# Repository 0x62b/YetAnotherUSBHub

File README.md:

# YetAnotherUSBHub
A 4-port low cost USB 2.0 hub with upstream USB-C and downstream USB-A x2, USB-C, and microSD.
wip onshape: https://cad.onshape.com/documents/d3076bcf5bdf960a68612e95/w/1076ab7133259d721c6eb065/e/0b541aa8461793eb55190b47?renderMode=0&uiState=6a0653a430b61269bd2de70a

## Repo Structure
`cad`: CAD files\
`pcb`: The KiCad PCB design files, and gerbers in `pcb/production`\
`bom.csv`: The BOM needed to assemble the PCB\

## BOM
|Item                               |Unit Price (AUD)|Quantity|Extended Price (AUD)|Extended Price (USD)       |Notes      |Link                                                 |
|-----------------------------------|----------------|--------|--------------------|---------------------------|-----------|-----------------------------------------------------|
|100nF 0402 capacitor               |0               |2       |0                   |0                          |Owned      |https://www.lcsc.com/product-detail/C60474.html      |
|10uF 0402 capacitor                |0               |7       |0                   |0                          |Owned      |https://www.lcsc.com/product-detail/C315248.html     |
|onsemi NSR0320MW2T1G               |0.16            |10      |1.6                 |1.18                       |MOQ 10     |https://www.lcsc.com/product-detail/C48192.html      |
|Green 0402 LED                     |0               |1       |0                   |0                          |Owned      |https://www.lcsc.com/product-detail/C598352.html     |
|Molex 67643-2911                   |1.34            |2       |2.68                |1.92                       |N/A        |https://www.lcsc.com/product-detail/C293351.html     |
|Molex 104031-0811                  |1.05            |1       |1.05                |0.75                       |N/A        |https://www.lcsc.com/product-detail/C585350.html     |
|Korean Hroparts Elec TYPE-C-31-M-12|0               |2       |0                   |0                          |Owned      |https://www.lcsc.com/product-detail/C165948.html     |
|1K 0402 resistor                   |0               |1       |0                   |0                          |Owned      |https://www.lcsc.com/product-detail/C106235.html     |
|5.1K 0402 resistor                 |0               |2       |0                   |0                          |Owned      |https://www.lcsc.com/product-detail/C105872.html     |
|56K 0402 resistor                  |0               |2       |0                   |0                          |Owned      |https://www.lcsc.com/product-detail/C114756.html     |
|CoreChips SL2.1A                   |1.65            |1       |1.65                |1.18                       |N/A        |https://www.lcsc.com/product-detail/C192893.html     |
|GENESYS GL823K-HCY04               |0.64            |1       |0.64                |0.46                       |N/A        |https://www.lcsc.com/product-detail/C284879.html     |
|TPD2E2U06DCK                       |0.21            |3       |1.05                |0.76                       |MOQ 5      |https://www.lcsc.com/product-detail/C1855726.html    |
|TPD6F003                           |0.93            |1       |0.93                |0.67                       |N/A        |https://www.lcsc.com/product-detail/C2863873.html    |
|2mm acrylic sheet                  |6.25            |1       |6.25                |4.53                       |200x200x2mm|https://www.aliexpress.com/item/32817321651.html     |
|PCB                                |-               |5       |-                   |5.3                        |N/A        |https://jlcpcb.com                                   |

## Cost
BOM (1 board + case): LCSC[6.92 USD + 3 USD handling + 9.38 USD shipping = 19.3 USD] + AliExpress[4.53 USD] = 23.83 USD\
PCB: 2 USD + 3.3 USD shipping = 5.3 USD\
Total: 29.13 USD (1 board + case)

## Assembly
Prerequisites: soldered PCB and printed case (PRINT THE CASE WITH +1-2% SCALE FOR TOLERANCES)

1. Mark out the dimensions of the acrylic window and use a scoring tool to cut it
2. From the sides, glue the acrylic window into the top case
3. Wait for glue to set
4. Place completed PCB into bottom case (optionally, affix it with double sided tape, but it should be held in place by friction anyway
5. Glue the top half onto bottom half (I tried, with this kind of size its not very feasible to use screws or anything)

## Images
### Schematic

### PCB layout

### PCB render

### Full render

The model may appear not to fit, but this was due to the export being messed up. it fits fine according to all my calculations and two braincells

### Zine

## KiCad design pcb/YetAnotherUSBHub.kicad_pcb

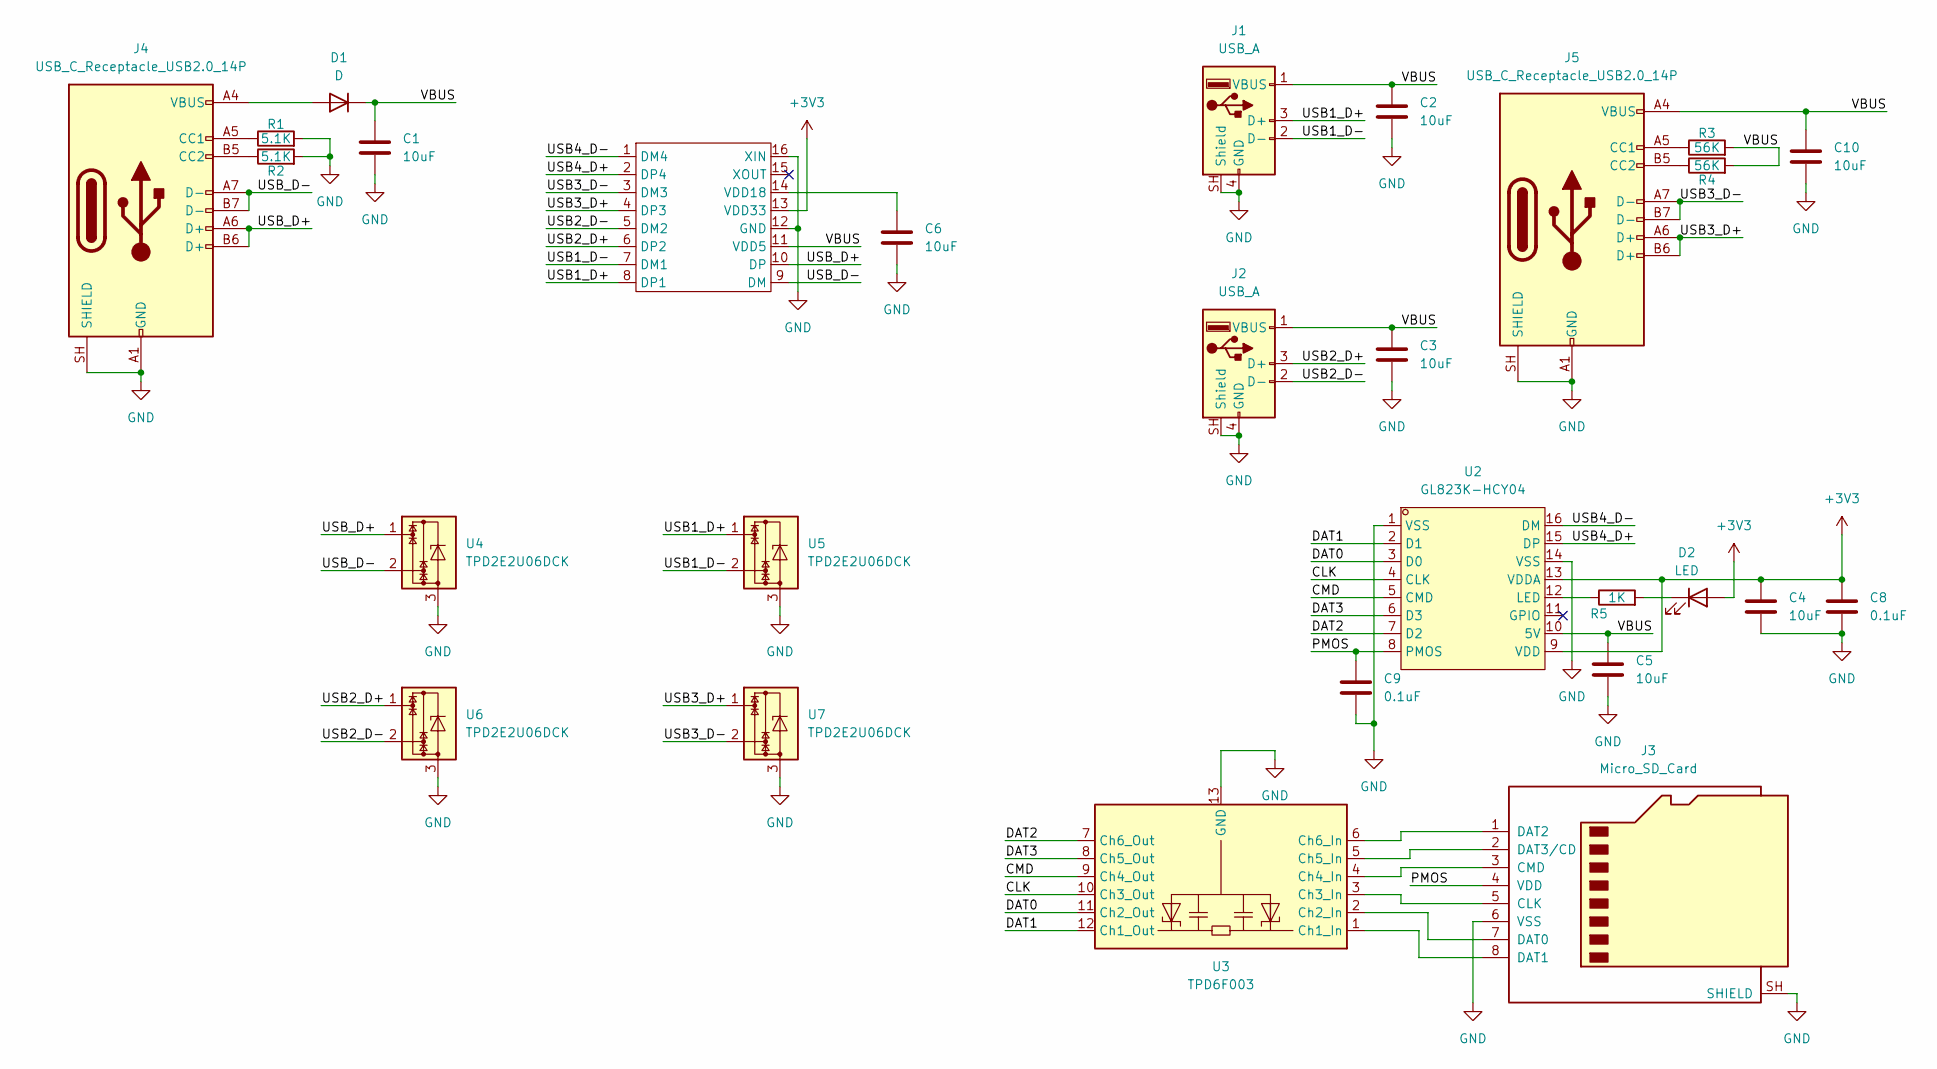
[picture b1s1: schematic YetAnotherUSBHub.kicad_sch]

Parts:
C1, C2, C3, C4, C5, C6, C10: 10uF; C_0402_1005Metric
C8, C9: 0.1uF; C_0402_1005Metric
D1: D; D_SOD-323
D2: LED; LED_0402_1005Metric
J1, J2: USB_A; USB_A_Molex_67643_Horizontal
J3: Micro_SD_Card; microSD_HC_Molex_104031-0811
J4, J5: USB_C_Receptacle_USB2.0_14P; USB_C_Receptacle_HRO_TYPE-C-31-M-12
R1, R2: 5.1K; R_0402_1005Metric
R3, R4: 56K; R_0402_1005Metric
R5: 1K; R_0402_1005Metric
U1: SOP-16_L10.0-W3.9-P1.27-LS6.0-BL
U2: GL823K-HCY04; SSOP-16_L4.9-W3.9-P0.64-LS6.0-BL; MPN GL823K-HCY04; LCSC Part C284879
U3: TPD6F003; Texas_R-PWSON-N12_EP0.4x2mm
U4, U5, U6, U7: TPD2E2U06DCK; SOT-323_SC-70

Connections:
+3V3: C4.1, C8.1, D2.2 (A), U1.13 (VDD33), U2.9 (VDD), U2.13 (VDDA)
/CLK: U2.4 (CLK), U3.10 (Ch3_Out)
/CMD: U2.5 (CMD), U3.9 (Ch4_Out)
/DAT0: U2.3 (D0), U3.11 (Ch2_Out)
/DAT1: U2.2 (D1), U3.12 (Ch1_Out)
/DAT2: U2.7 (D2), U3.7 (Ch6_Out)
/DAT3: U2.6 (D3), U3.8 (Ch5_Out)
/PMOS: C9.1, J3.4 (VDD), U2.8 (PMOS)
/USB1_D+: J1.3 (D+), U1.8 (DP1), U5.1
/USB1_D-: J1.2 (D-), U1.7 (DM1), U5.2
/USB2_D+: J2.3 (D+), U1.6 (DP2), U6.1
/USB2_D-: J2.2 (D-), U1.5 (DM2), U6.2
/USB3_D+: J5.A6 (D+), J5.B6 (D+), U1.4 (DP3), U7.1
/USB3_D-: J5.A7 (D-), J5.B7 (D-), U1.3 (DM3), U7.2
/USB4_D+: U1.2 (DP4), U2.15 (DP)
/USB4_D-: U1.1 (DM4), U2.16 (DM)
/USB_D+: J4.A6 (D+), J4.B6 (D+), U1.10 (DP), U4.1
/USB_D-: J4.A7 (D-), J4.B7 (D-), U1.9 (DM), U4.2
/VBUS: C1.1, C2.1, C3.1, C5.1, C10.1, D1.1 (K), J1.1 (VBUS), J2.1 (VBUS), J5.A4 (VBUS), J5.A9 (VBUS), J5.B4 (VBUS), J5.B9 (VBUS), R3.2, R4.2, U1.11 (VDD5), U2.10 (5V)
GND: C1.2, C2.2, C3.2, C4.2, C5.2, C6.2, C8.2, C9.2, C10.2, J1.4 (GND), J1.SH (Shield), J2.4 (GND), J2.SH (Shield), J3.6 (VSS), J3.SH (SHIELD), J4.A1 (GND), J4.A12 (GND), J4.B1 (GND), J4.B12 (GND), J4.SH (SHIELD), J5.A1 (GND), J5.A12 (GND), J5.B1 (GND), J5.B12 (GND), J5.SH (SHIELD), R1.2, R2.2, U1.12 (GND), U1.16 (XIN), U2.1 (VSS), U2.14 (VSS), U3.13 (GND), U4.3, U5.3, U6.3, U7.3
unnamed: D1.2 (A), J4.A4 (VBUS), J4.A9 (VBUS), J4.B4 (VBUS), J4.B9 (VBUS)
unnamed: D2.1 (K), R5.2
unnamed: J3.5 (CLK), U3.3 (Ch3_In)
unnamed: J3.3 (CMD), U3.4 (Ch4_In)
unnamed: J3.7 (DAT0), U3.2 (Ch2_In)
unnamed: J3.8 (DAT1), U3.1 (Ch1_In)
unnamed: J3.1 (DAT2), U3.6 (Ch6_In)
unnamed: J3.2 (DAT3/CD), U3.5 (Ch5_In)
unnamed: J4.A5 (CC1), R1.1
unnamed: J4.B5 (CC2), R2.1
unnamed: J5.A5 (CC1), R3.1
unnamed: J5.B5 (CC2), R4.1
unnamed: C6.1, U1.14 (VDD18)
unnamed: R5.1, U2.12 (LED)

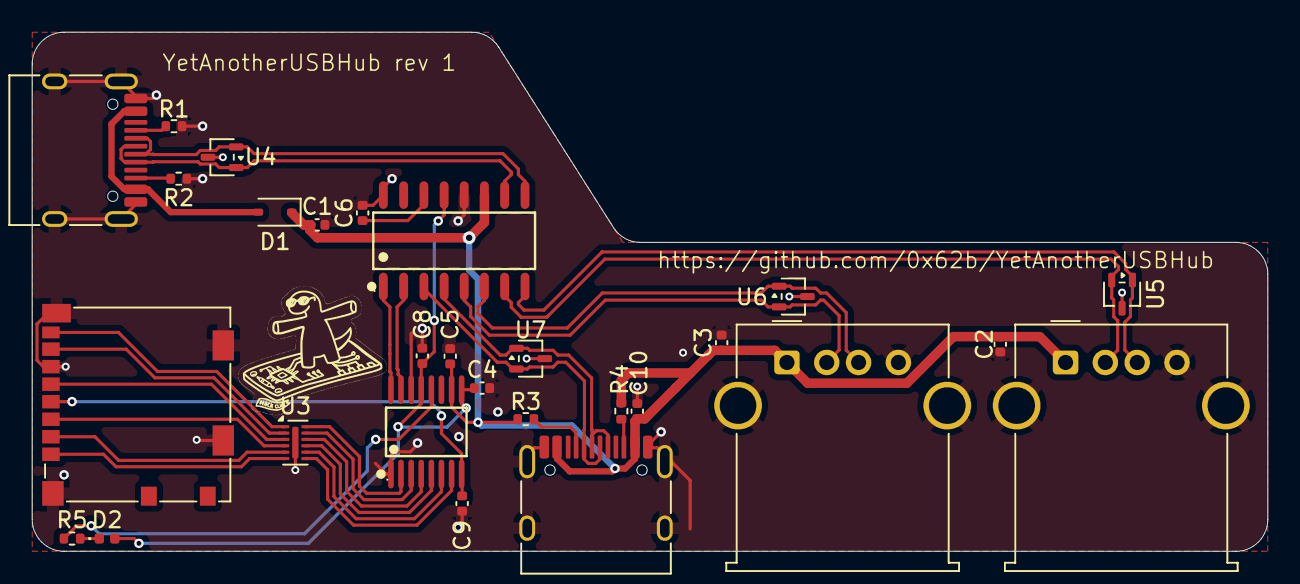
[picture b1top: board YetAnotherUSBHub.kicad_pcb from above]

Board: 2 copper layers, 77.6 x 32.6 mm, 28 parts (0 on the bottom side), 34 nets.

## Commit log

2026-05-13 cad files
2026-05-13 stuff
2026-05-13 add .history to gitignore
2026-05-13 add assembly instructions, add case hardware to bom
2026-05-13 add zine
2026-05-13 fix table
2026-05-13 zine fonts
2026-05-29 new bom
2026-05-29 esd protection on pcb
2026-05-29 Remove lcsc.csv
2026-05-29 update zine with new render + info
2026-05-30 add render
2026-05-30 new zine to readme
2026-05-30 new board export
2026-05-30 new render to zine
2026-05-30 update case cad files
